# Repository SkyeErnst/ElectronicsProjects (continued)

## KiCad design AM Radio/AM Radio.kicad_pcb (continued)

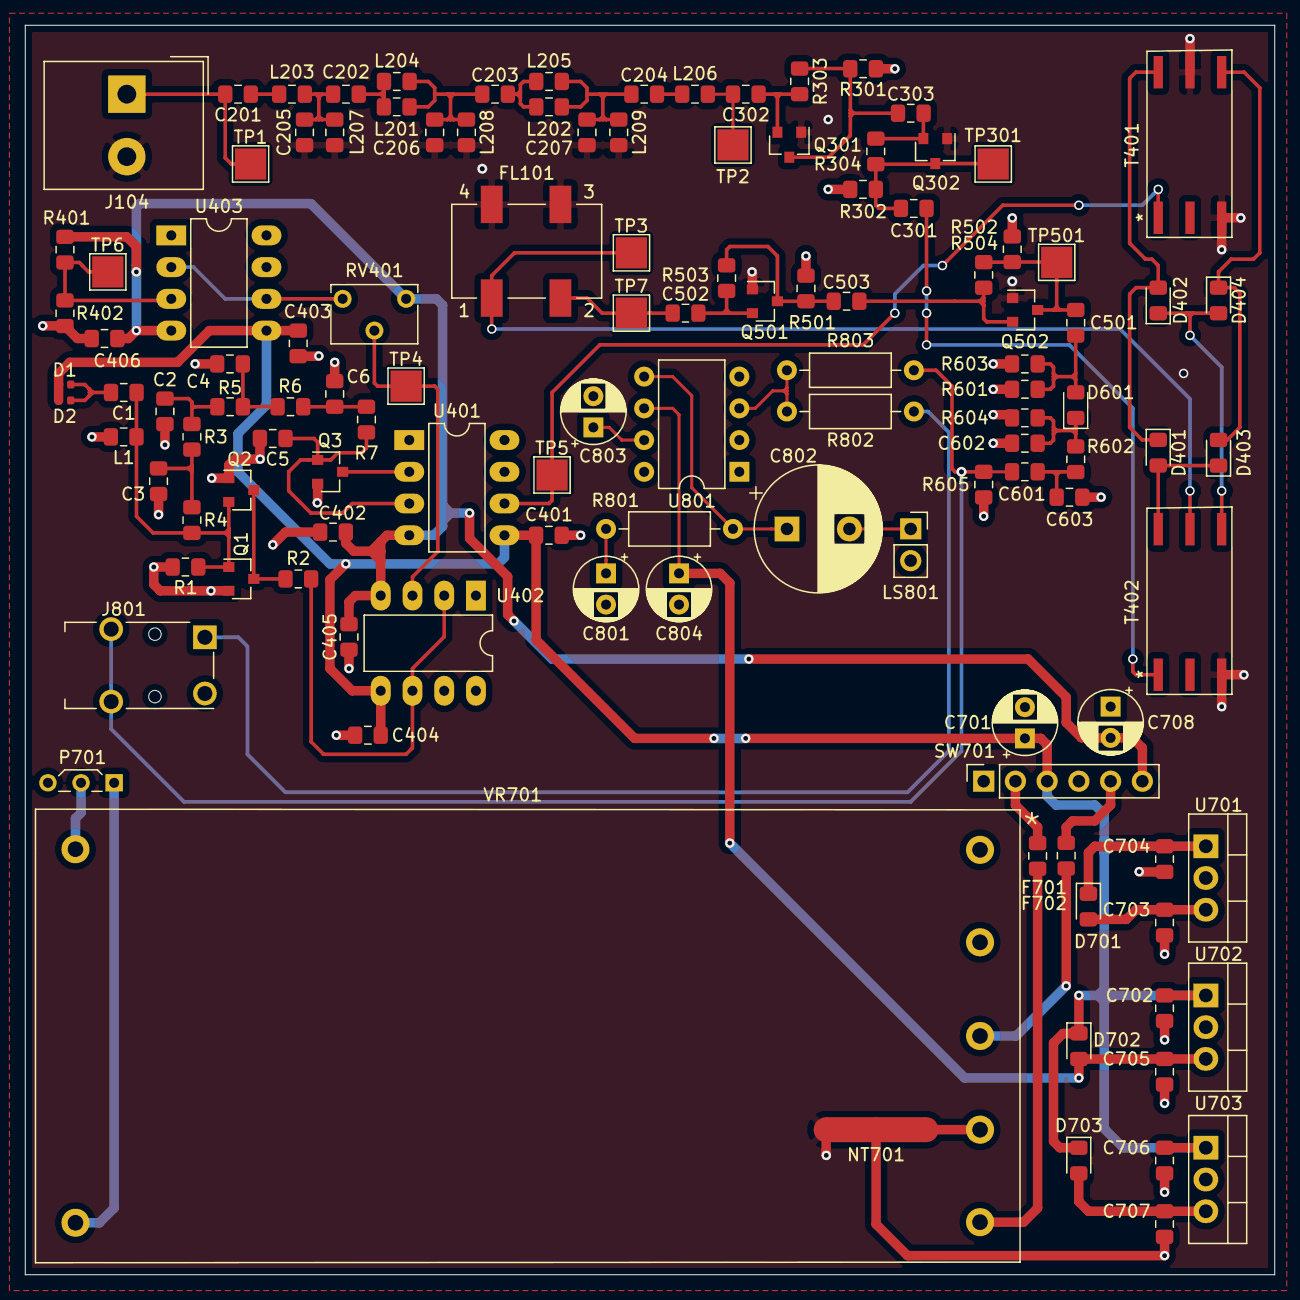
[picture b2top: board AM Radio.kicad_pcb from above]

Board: 4 copper layers, 100.0 x 100.0 mm, 121 parts (0 on the bottom side), 62 nets.

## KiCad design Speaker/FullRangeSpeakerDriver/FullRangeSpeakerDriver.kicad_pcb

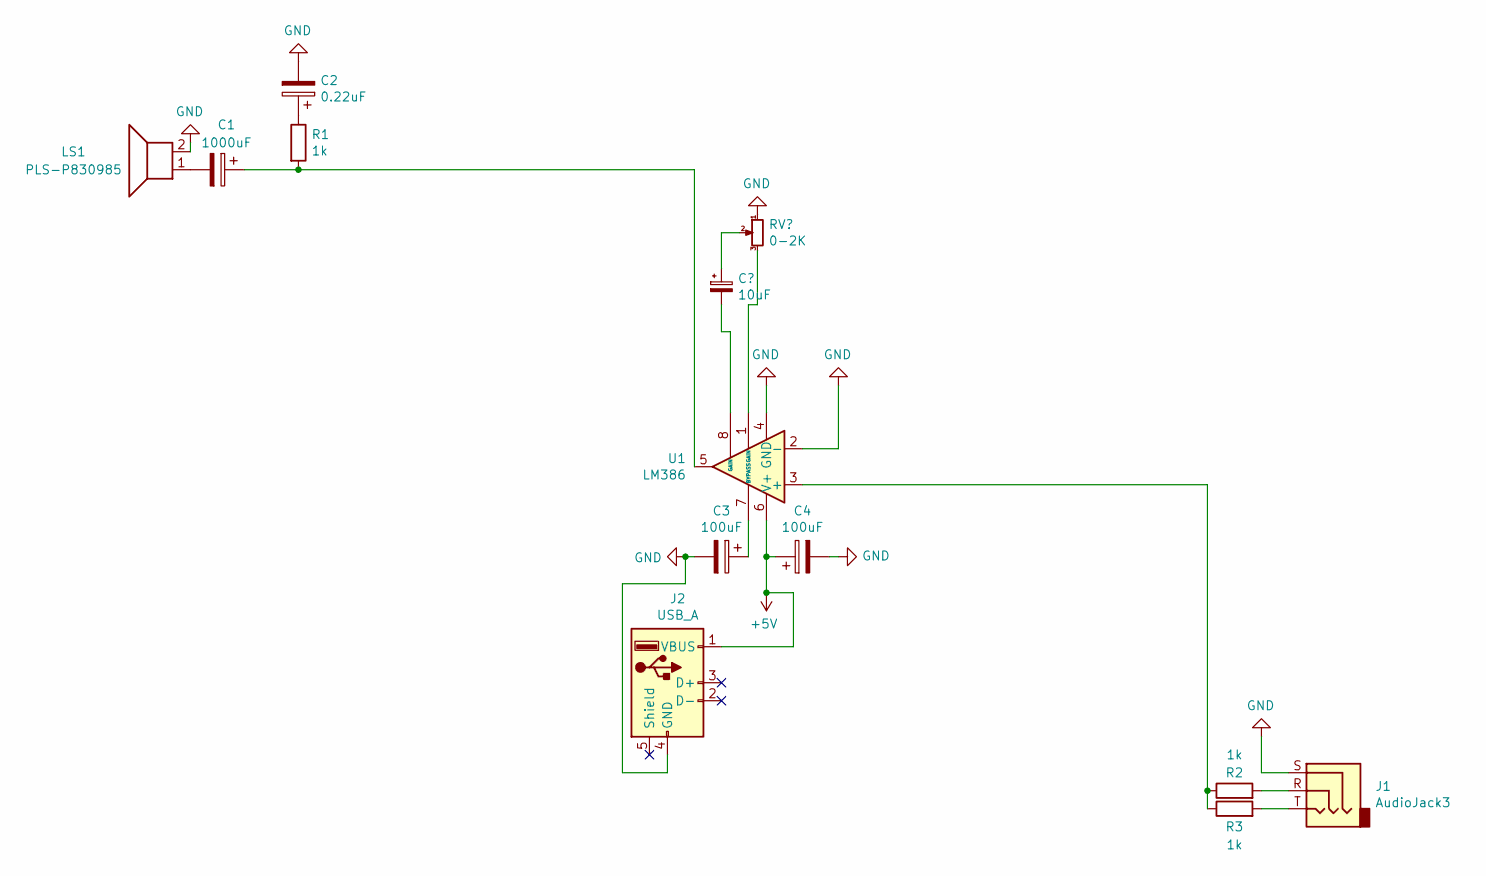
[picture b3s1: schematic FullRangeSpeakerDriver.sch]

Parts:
C1: 1000uF; CP_Radial_D10.0mm_P5.00mm
C2: 0.22uF; CP_Radial_D5.0mm_P2.50mm
C3, C4: 100uF; CP_Radial_D5.0mm_P2.50mm
J1: AudioJack3; PinSocket_1x03_P2.54mm_Vertical
J2: USB_A; USB_A_Stewart_SS-52100-001_Horizontal
LS1: PLS-P830985; PinSocket_1x02_P2.54mm_Vertical
R1, R2, R3: 1k; R_Axial_DIN0207_L6.3mm_D2.5mm_P10.16mm_Horizontal
U1: LM386; DIP-8_W7.62mm

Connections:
+15V: C4.1, J2.1 (VBUS), U1.6 (V+)
GND: C2.2, C3.2, C4.2, J1.S, J2.4 (GND), LS1.2, U1.2 (-), U1.4 (GND)
unnamed: C1.1, R1.2, U1.5
unnamed: C1.2, LS1.1
unnamed: C2.1, R1.1
unnamed: C3.1, U1.7 (BYPASS)
unnamed: J1.R, R2.2
unnamed: J1.T, R3.2
unnamed: R2.1, R3.1, U1.3 (+)

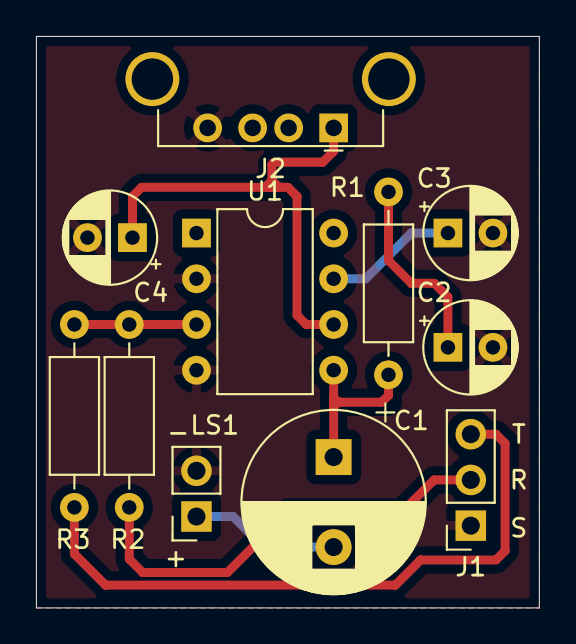
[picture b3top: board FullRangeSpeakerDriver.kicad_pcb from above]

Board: 2 copper layers, 27.9 x 31.7 mm, 11 parts (0 on the bottom side), 9 nets.

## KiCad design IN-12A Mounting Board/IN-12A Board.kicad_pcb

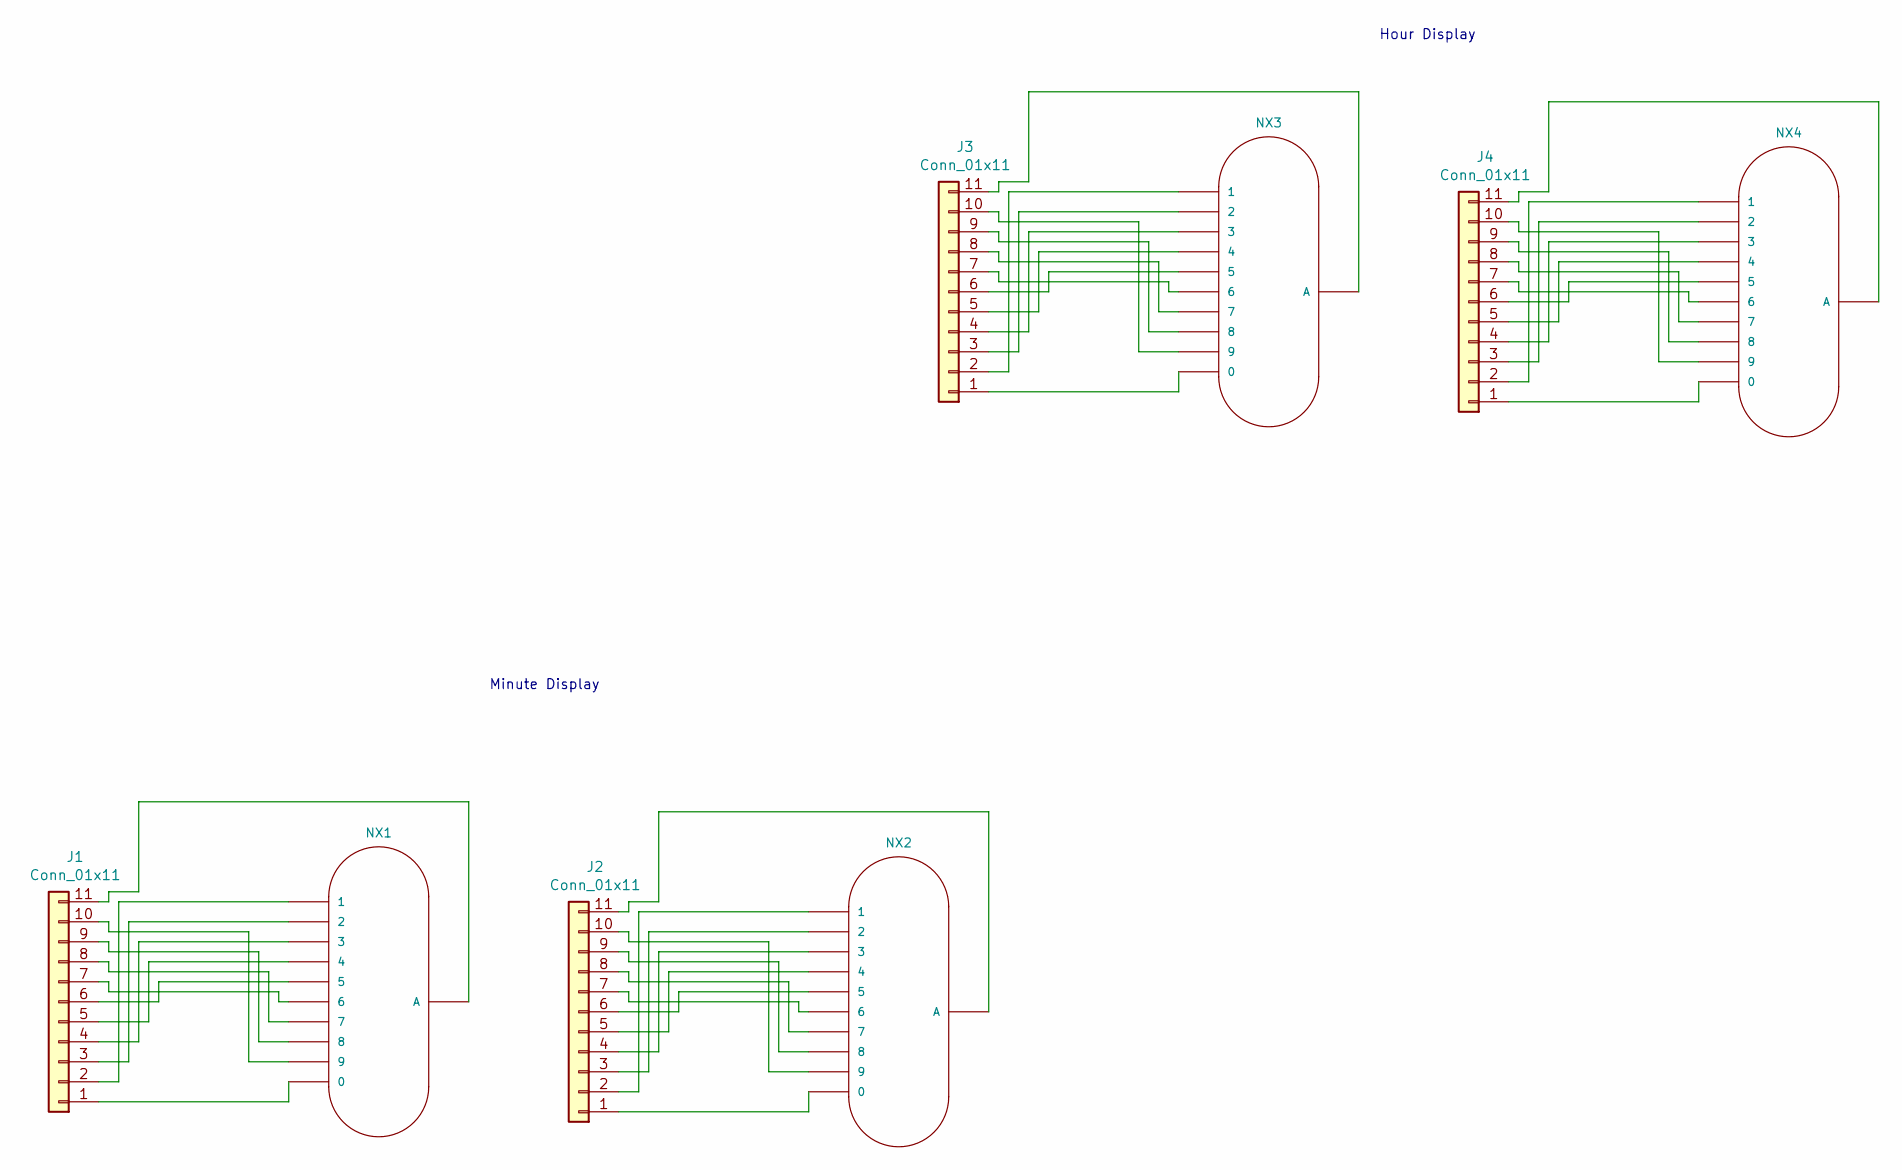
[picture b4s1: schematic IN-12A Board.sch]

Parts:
J1, J2, J3, J4: Conn_01x11; PinHeader_1x11_P2.54mm_Vertical
NX1, NX2, NX3, NX4: IN-12A; nixies-us-IN-12

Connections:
unnamed: J1.1, NX1.0
unnamed: J1.2, NX1.1
unnamed: J1.3, NX1.2
unnamed: J1.4, NX1.3
unnamed: J1.5, NX1.4
unnamed: J1.6, NX1.5
unnamed: J1.7, NX1.6
unnamed: J1.8, NX1.7
unnamed: J1.9, NX1.8
unnamed: J1.10, NX1.9
unnamed: J1.11, NX1.A
unnamed: J2.1, NX2.0
unnamed: J2.2, NX2.1
unnamed: J2.3, NX2.2
unnamed: J2.4, NX2.3
unnamed: J2.5, NX2.4
unnamed: J2.6, NX2.5
unnamed: J2.7, NX2.6
unnamed: J2.8, NX2.7
unnamed: J2.9, NX2.8
unnamed: J2.10, NX2.9
unnamed: J2.11, NX2.A
unnamed: J3.1, NX3.0
unnamed: J3.2, NX3.1
unnamed: J3.3, NX3.2
unnamed: J3.4, NX3.3
unnamed: J3.5, NX3.4
unnamed: J3.6, NX3.5
unnamed: J3.7, NX3.6
unnamed: J3.8, NX3.7
unnamed: J3.9, NX3.8
unnamed: J3.10, NX3.9
unnamed: J3.11, NX3.A
unnamed: J4.1, NX4.0
unnamed: J4.2, NX4.1
unnamed: J4.3, NX4.2
unnamed: J4.4, NX4.3
unnamed: J4.5, NX4.4
unnamed: J4.6, NX4.5
unnamed: J4.7, NX4.6
unnamed: J4.8, NX4.7
unnamed: J4.9, NX4.8
unnamed: J4.10, NX4.9
unnamed: J4.11, NX4.A

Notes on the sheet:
Hour Display
Minute Display

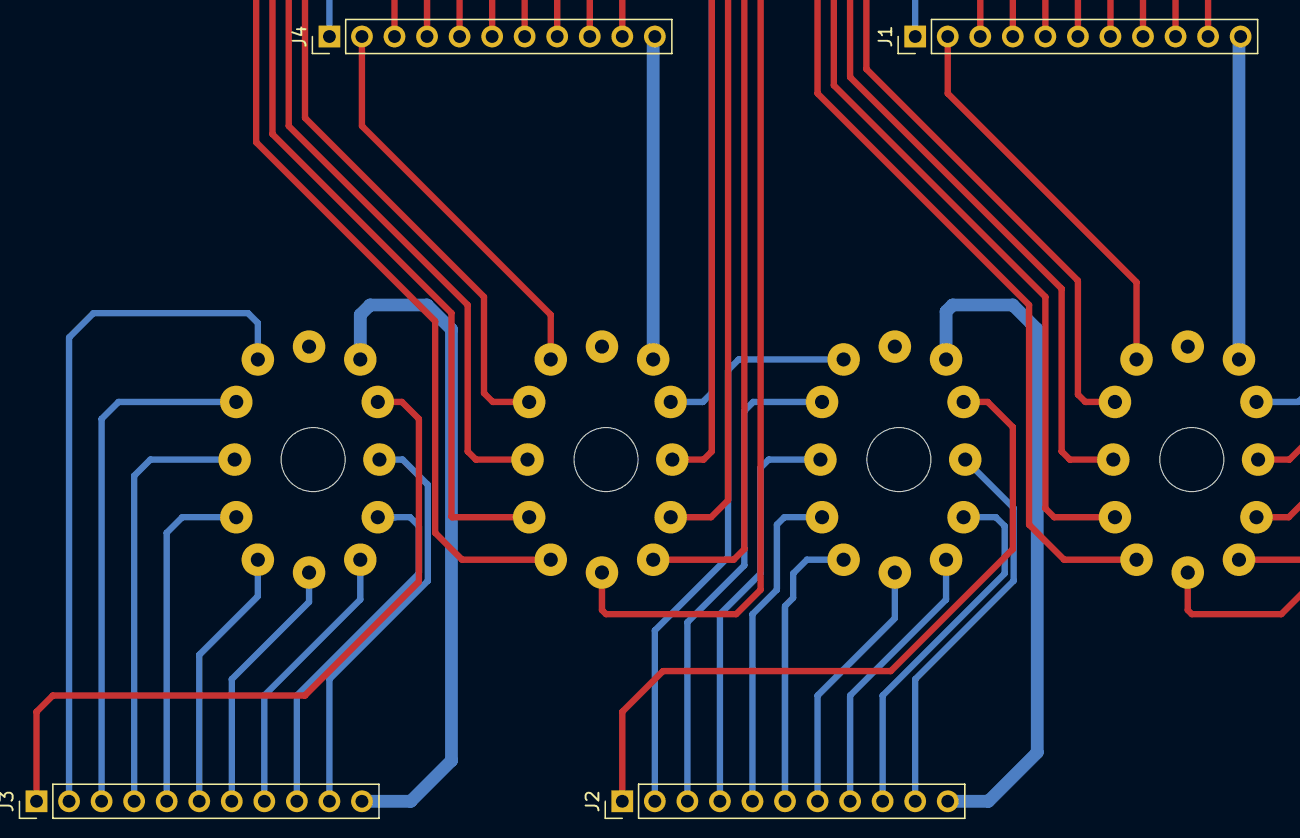
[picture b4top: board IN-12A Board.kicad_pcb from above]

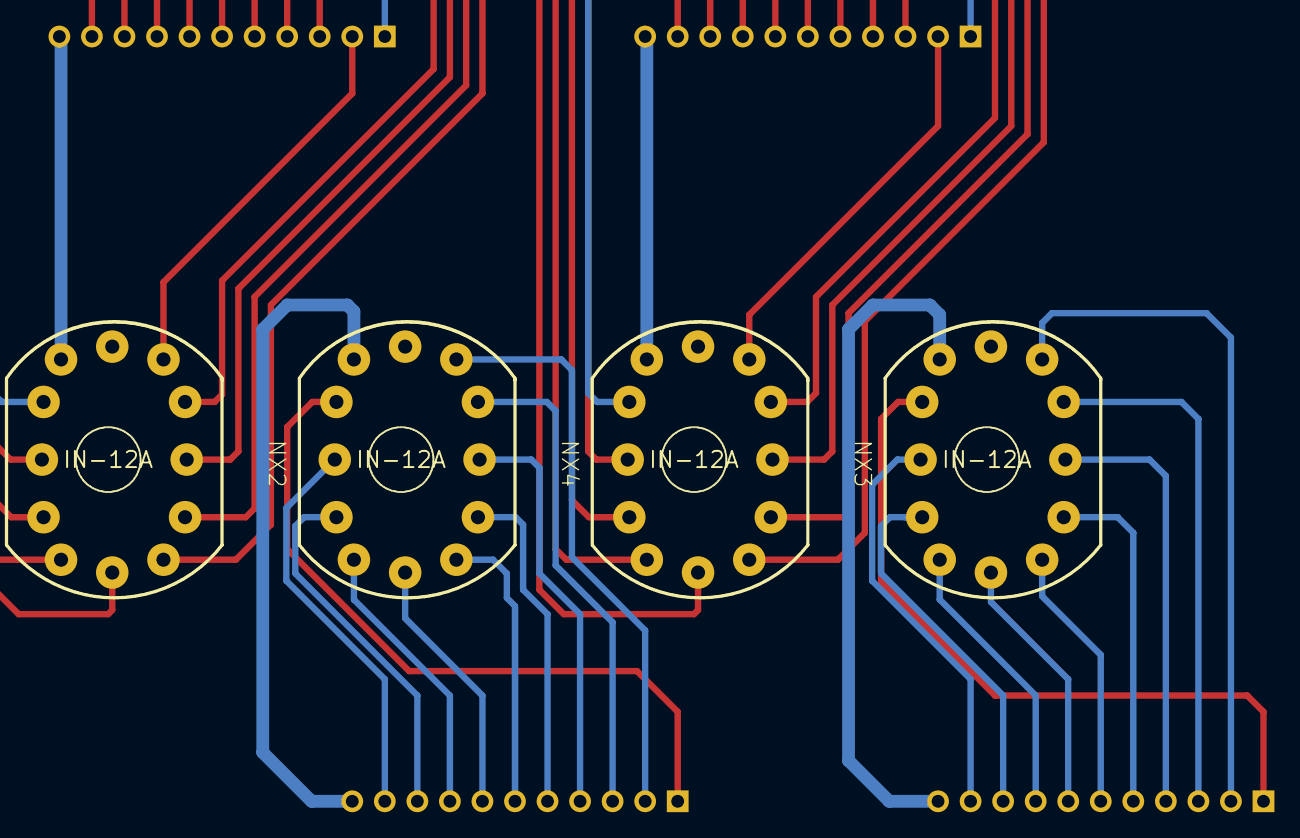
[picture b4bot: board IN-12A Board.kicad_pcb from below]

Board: 2 copper layers, 8 parts (4 on the bottom side), 44 nets.

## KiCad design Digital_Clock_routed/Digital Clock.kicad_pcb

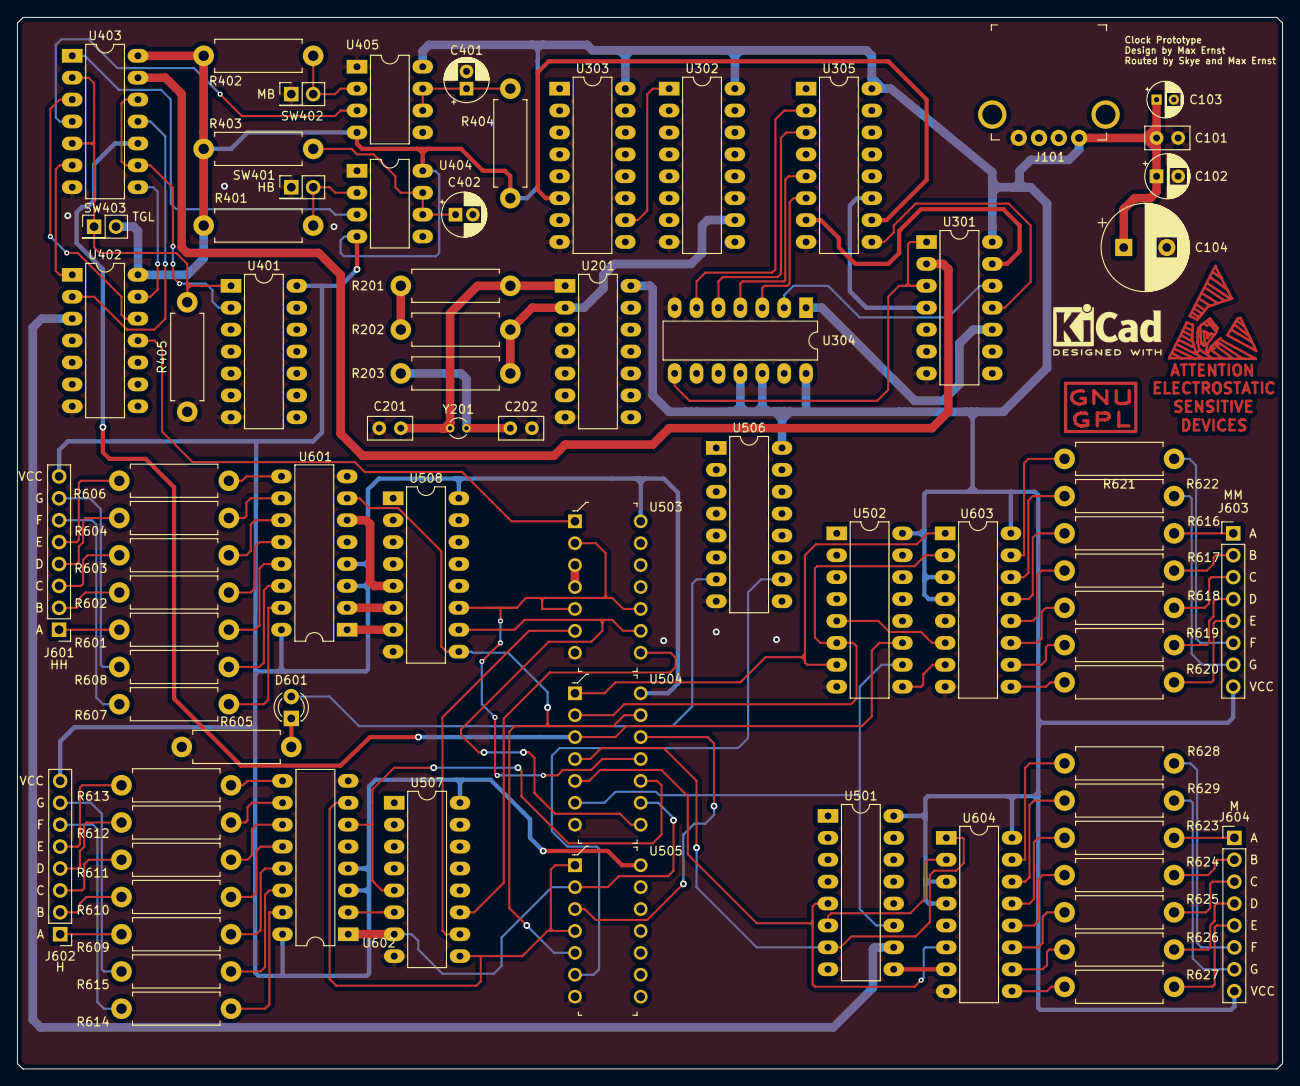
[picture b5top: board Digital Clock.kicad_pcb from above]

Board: 2 copper layers, 146.7 x 121.9 mm, 78 parts (0 on the bottom side), 116 nets.

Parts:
C101: 100nF; C_Disc_D5.0mm_W2.5mm_P2.50mm
C102: 1uF; CP_Radial_D5.0mm_P2.50mm
C103: 47uF; CP_Radial_D4.0mm_P2.00mm
C104: 1000uF; CP_Radial_D10.0mm_P5.00mm
C201, C202: 22pF; C_Disc_D5.0mm_W2.5mm_P2.50mm
C401, C402: 0.22uF; CP_Radial_D5.0mm_P2.00mm
D601: GREEN; LED_D3.0mm
J101: USB_A; USB_A_Female_UE27AC54100
J601, J602, J603, J604: Conn_01x08; PinHeader_1x08_P2.54mm_Vertical
R201, R202: 6.5Meg; R_Axial_DIN0411_L9.9mm_D3.6mm_P12.70mm_Horizontal
R203: 270k; R_Axial_DIN0411_L9.9mm_D3.6mm_P12.70mm_Horizontal
R401, R402, R405: 1k; R_Axial_DIN0411_L9.9mm_D3.6mm_P12.70mm_Horizontal
R403, R404: 1Meg; R_Axial_DIN0411_L9.9mm_D3.6mm_P12.70mm_Horizontal
R601, R602, R603, R604, R606, R607, R608, R609, R610, R611, R612, R613, R614, R615, R616, R617, R618, R619, R620, R621, R622, R623, R624, R625, R626, R627, R628, R629: 24; R_Axial_DIN0411_L9.9mm_D3.6mm_P12.70mm_Horizontal
R605: 220; R_Axial_DIN0411_L9.9mm_D3.6mm_P12.70mm_Horizontal
SW401: Hour_Button; PinHeader_2x01_P2.54mm_Vertical
SW402: Minute_Button; PinHeader_2x01_P2.54mm_Vertical
SW403: Toggle_Switch; PinHeader_2x01_P2.54mm_Vertical
U201: 74HCU04E; DIP-14_W7.62mm_LongPads
U301, U401: 74S04; DIP-14_W7.62mm_LongPads
U302, U303, U305: SN74HC4040N; DIP-16_W7.62mm_LongPads
U304: CD74HC30E; DIP-14_W7.62mm_LongPads
U402: SN74LS32N; DIP-14_W7.62mm_LongPads
U403: SN74HCT08N; DIP-14_W7.62mm_LongPads
U404, U405: NE555; DIP-8_W7.62mm_LongPads
U501, U502, U506, U507, U508: 4040; DIP-16_W7.62mm_LongPads
U503: SN74LS32N; DIP-14_W3mm
U504: SN74LS08N; DIP-14_W3mm
U505: SN74ALS08N; DIP-14_W3mm
U601, U602, U603, U604: 7447; DIP-16_W7.62mm_LongPads
Y201: 32.768kHz; Crystal_Round_D2.0mm_Vertical

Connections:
+5V: C101.1, C102.1, C103.1, C104.1, J101.1, J601.8, J602.8, J603.8, J604.8, R401.2, R402.2, R403.1, R404.1, SW403.2, U201.14, U301.14, U302.16, U303.16, U304.11, U304.12, U304.14, U305.16, U401.14, U402.14, U403.14, U404.4, U404.8, U405.4, U405.8, U501.16, U502.16, U503.14, U504.14, U505.14, U506.16, U507.16, U508.16, U601.3, U601.4, U601.16, U602.3, U602.4, U602.16, U603.3, U603.4, U603.16, U604.3, U604.4, U604.16
/ButtonLogic/1stPlaceHoursInput: U402.11, U503.1
/ButtonLogic/1stPlaceMinutesInput: U402.3, U501.10
/ButtonLogic/MinutesOutput: U403.10, U502.11, U504.3
/ButtonLogic/SecondsOutput: U301.2, U403.13
/DisplaySection/1stP_HH_O: U504.13, U505.5, U508.9, U601.7
/DisplaySection/1stP_H_O: U505.1, U505.4, U507.9, U602.7
/DisplaySection/1stP_MM_O: U502.9, U603.7
/DisplaySection/1stP_M_O: U501.9, U604.7
/DisplaySection/2ndP_HH_O: U508.7, U601.1
/DisplaySection/2ndP_H_O: U504.9, U505.2, U507.7, U602.1
/DisplaySection/2ndP_MM_O: U502.7, U504.1, U603.1
/DisplaySection/2ndP_M_O: U501.7, U504.4, U604.1
/DisplaySection/3rdP_HH_O: U508.6, U601.2
/DisplaySection/3rdP_H_O: U507.6, U602.2
/DisplaySection/3rdP_MM_O: U502.6, U504.2, U603.2
/DisplaySection/3rdP_M_O: U501.6, U604.2
/DisplaySection/4thP_HH_O: U508.5, U601.6
/DisplaySection/4thP_H_O: U504.10, U507.5, U602.6
/DisplaySection/4thP_MM_O: U502.5, U603.6
/DisplaySection/4thP_M_O: U501.5, U504.5, U604.6
/DisplaySection/AM_PM_INDICATOR: D601.2, U506.7
/Oscillator/Oscillator32768Output: R202.1, R203.1, U201.2, U302.10
GND: C101.2, C102.2, C103.2, C104.2, C201.2, C202.2, C401.2, C402.2, J101.4, R405.1, R605.1, SW401.1, SW402.1, U201.7, U301.7, U302.8, U302.11, U303.8, U303.11, U304.7, U305.8, U401.7, U402.7, U403.7, U404.1, U405.1, U501.8, U502.8, U503.7, U504.7, U505.7, U506.8, U507.8, U508.8, U601.8, U602.8, U603.8, U604.8
unnamed: C201.1, R201.2, U201.1, Y201.1
unnamed: C202.1, R203.2, Y201.2
unnamed: C401.1, R404.2, U405.6, U405.7
unnamed: C402.1, R403.2, U404.6, U404.7
unnamed: D601.1, R605.2
unnamed: J601.1, R601.1
unnamed: J601.2, R602.1
unnamed: J601.3, R603.1
unnamed: J601.4, R604.1
unnamed: J601.5, R606.1
unnamed: J601.6, R607.1
unnamed: J601.7, R608.1
unnamed: J602.1, R609.1
unnamed: J602.2, R610.1
unnamed: J602.3, R611.1
unnamed: J602.4, R612.1
unnamed: J602.5, R613.1
unnamed: J602.6, R614.1
unnamed: J602.7, R615.1
unnamed: J603.1, R616.1
unnamed: J603.2, R617.1
unnamed: J603.3, R618.1
unnamed: J603.4, R619.1
unnamed: J603.5, R620.1
unnamed: J603.6, R621.1
unnamed: J603.7, R622.1
unnamed: J604.1, R623.1
unnamed: J604.2, R624.1
unnamed: J604.3, R625.1
unnamed: J604.4, R626.1
unnamed: J604.5, R627.1
unnamed: J604.6, R628.1
unnamed: J604.7, R629.1
unnamed: R201.1, R202.2
unnamed: R401.1, SW401.2, U404.2
unnamed: R402.1, SW402.2, U405.2
unnamed: R405.2, SW403.1, U401.1, U403.2, U403.5
unnamed: R601.2, U601.13
unnamed: R602.2, U601.12
unnamed: R603.2, U601.11
unnamed: R604.2, U601.10
unnamed: R606.2, U601.9
unnamed: R607.2, U601.15
unnamed: R608.2, U601.14
unnamed: R609.2, U602.13
unnamed: R610.2, U602.12
unnamed: R611.2, U602.11
unnamed: R612.2, U602.10
unnamed: R613.2, U602.9
unnamed: R614.2, U602.15
unnamed: R615.2, U602.14
unnamed: R616.2, U603.13
unnamed: R617.2, U603.12
unnamed: R618.2, U603.11
unnamed: R619.2, U603.10
unnamed: R620.2, U603.9
unnamed: R621.2, U603.15
unnamed: R622.2, U603.14
unnamed: R623.2, U604.13
unnamed: R624.2, U604.12
unnamed: R625.2, U604.11
unnamed: R626.2, U604.10
unnamed: R627.2, U604.9
unnamed: R628.2, U604.15
unnamed: R629.2, U604.14
unnamed: U301.1, U301.3, U304.8
unnamed: U301.4, U305.11
unnamed: U301.10, U304.1
unnamed: U301.11, U305.9
unnamed: U301.12, U304.2
unnamed: U301.13, U305.7
unnamed: U302.1, U303.10
unnamed: U303.6, U305.10
unnamed: U304.3, U305.6
unnamed: U304.4, U305.5
unnamed: U304.5, U305.3
unnamed: U304.6, U305.2
unnamed: U401.2, U403.9, U403.12
unnamed: U402.1, U403.6
unnamed: U402.2, U403.11
unnamed: U402.12, U403.3
unnamed: U402.13, U403.8
unnamed: U403.1, U404.3
unnamed: U403.4, U405.3
unnamed: U501.11, U502.10, U504.6
unnamed: U503.3, U503.4
unnamed: U503.6, U507.10
unnamed: U503.8, U507.11
unnamed: U503.9, U504.8, U508.10
unnamed: U503.2, U503.5, U503.10, U504.11, U508.11
unnamed: U504.12, U505.3
unnamed: U505.6, U506.10

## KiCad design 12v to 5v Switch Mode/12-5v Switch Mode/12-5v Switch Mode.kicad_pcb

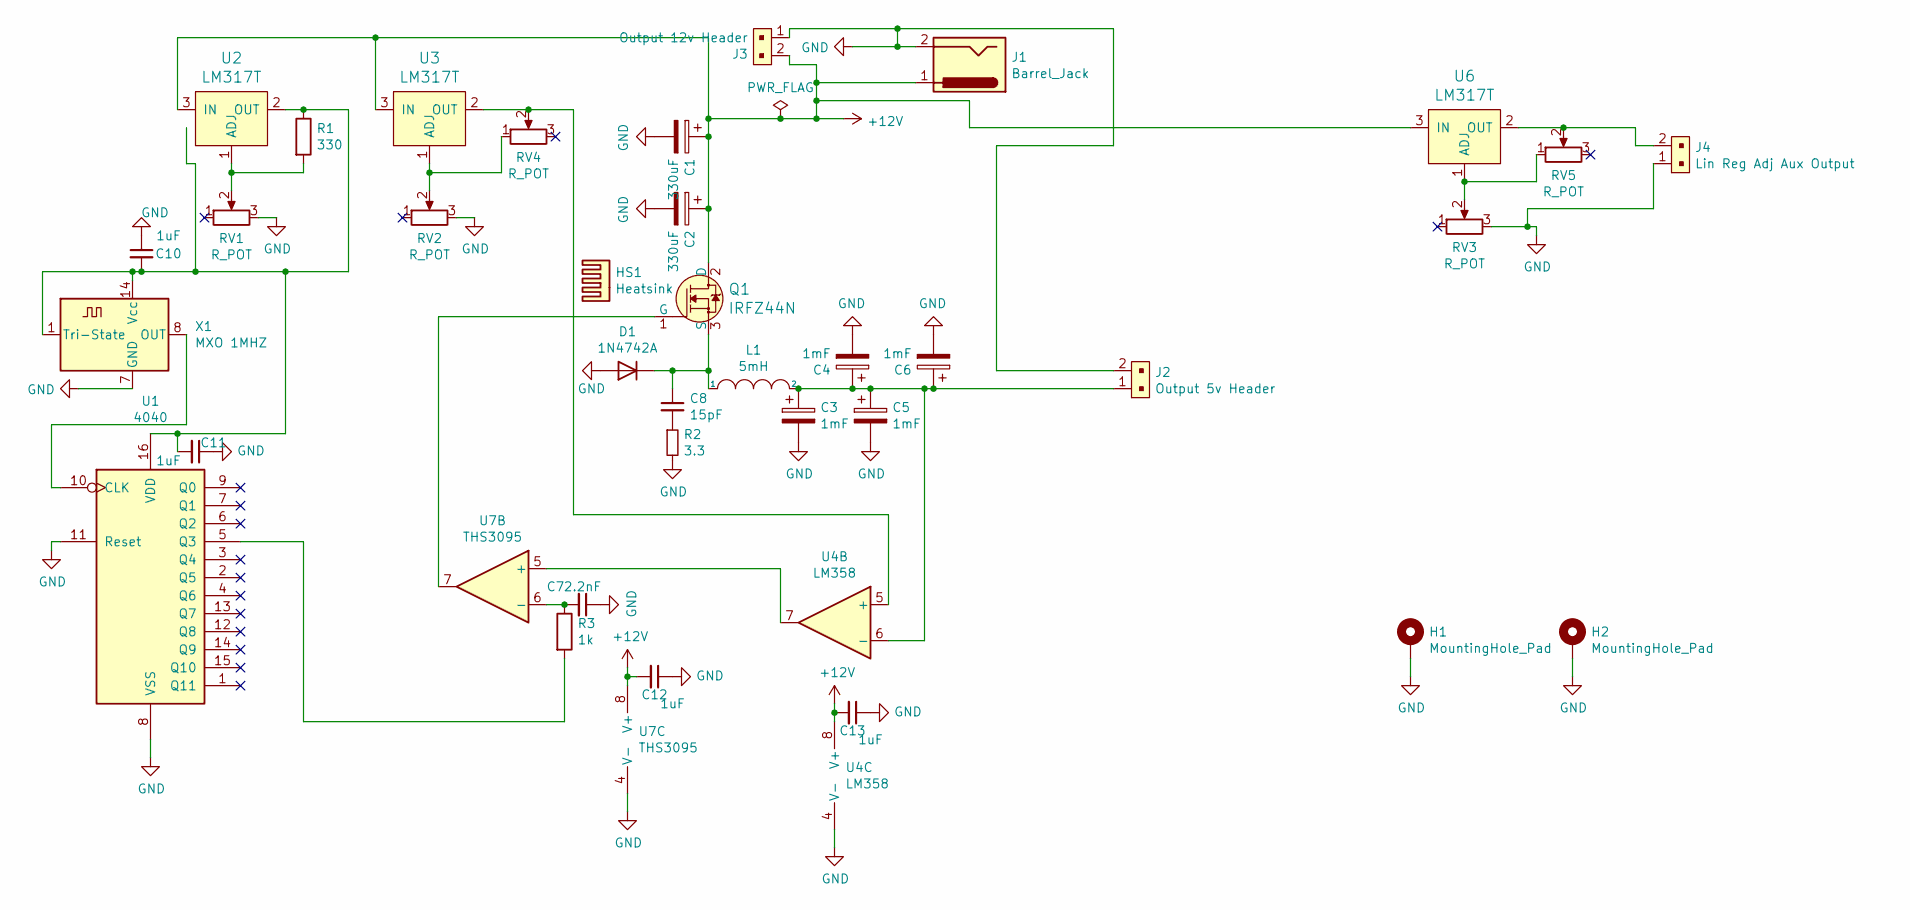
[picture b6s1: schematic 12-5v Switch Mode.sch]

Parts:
C1, C2: 330uF; CP_Radial_D12.5mm_P5.00mm
C3, C4, C5, C6: 1mF; CP_Radial_D12.5mm_P5.00mm
C7: 2.2nF; CP_Radial_D4.0mm_P1.50mm
C8: 15pF; CP_Radial_D4.0mm_P1.50mm
C10, C11, C12, C13: 1uF; C_0805_2012Metric
D1: 1N4742A; D_DO-41_SOD81_P7.62mm_Horizontal
H1, H2: MountingHole_Pad; MountingHole_2.2mm_M2_Pad
HS1: Heatsink; Heatsink VM1-038-1AE
J1: Barrel_Jack; CUI_PJ-063AH
J2: Output 5v Header; PinHeader_1x2_P2.54mm; MPN 22-23-2021; Digi-Key_PN WM4200-ND
J3: Output 12v Header; PinHeader_1x2_P2.54mm; MPN 22-23-2021; Digi-Key_PN WM4200-ND
J4: Lin Reg Adj Aux Output; PinHeader_1x2_P2.54mm; MPN 22-23-2021; Digi-Key_PN WM4200-ND
L1: 5mH; L_Radial_D50.8mm_P33.27mm_Vishay_IHB-6
Q1: IRFZ44N; TO-220-3; MPN IRFZ44N; Digi-Key_PN IRFZ44N
R1: 330; R_Axial_DIN0207_L6.3mm_D2.5mm_P10.16mm_Horizontal
R2: 3.3; R_Axial_DIN0207_L6.3mm_D2.5mm_P10.16mm_Horizontal
R3: 1k; R_Axial_DIN0207_L6.3mm_D2.5mm_P10.16mm_Horizontal
RV1, RV2, RV3, RV4, RV5: R_POT; Potentiometer_Bourns_3299W_Vertical
U1: 4040; DIP-16_W7.62mm
U2, U3, U6: LM317T; TO-220-3; MPN LM317T; Digi-Key_PN 497-1575-5-ND
U4: LM358; DIP-8_W7.62mm
U7: THS3095; SOIC-8_3.9x4.9mm_P1.27mm
X1: MXO 1MHZ; Oscillator_DIP-14

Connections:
+12V: C1.1, C2.1, C12.2, C13.2, J1.1, J3.2, Q1.2 (D), U2.3 (IN), U3.3 (IN), U4.8 (V+), U6.3 (IN), U7.8 (V+)
GND: C1.2, C2.2, C3.2, C4.2, C5.2, C6.2, C7.1, C10.1, C11.1, C12.1, C13.1, D1.1 (A), H1.1, H2.1, J1.2, J2.2, J3.1, J4.1, R2.2, RV1.3, RV2.3, RV3.3, U1.8 (VSS), U1.11 (Reset), U4.4 (V-), U7.4 (V-), X1.7 (GND)
unnamed: C3.1, C4.1, C5.1, C6.1, J2.1, L1.2, U4.6 (-)
unnamed: C7.2, R3.1, U7.6 (-)
unnamed: C8.1, D1.2 (K), L1.1, Q1.3 (S)
unnamed: C8.2, R2.1
unnamed: C10.2, C11.2, R1.1, U1.16 (VDD), U2.2 (OUT), X1.1 (Tri-State), X1.14 (Vcc)
unnamed: J4.2, RV5.2, U6.2 (OUT)
unnamed: Q1.1 (G), U7.7
unnamed: R1.2, RV1.2, U2.1 (ADJ)
unnamed: R3.2, U1.5 (Q3)
unnamed: RV2.2, RV4.1, U3.1 (ADJ)
unnamed: RV3.2, RV5.1, U6.1 (ADJ)
unnamed: RV4.2, U3.2 (OUT), U4.5 (+)
unnamed: U1.10 (CLK), X1.8 (OUT)
unnamed: U4.7, U7.5 (+)

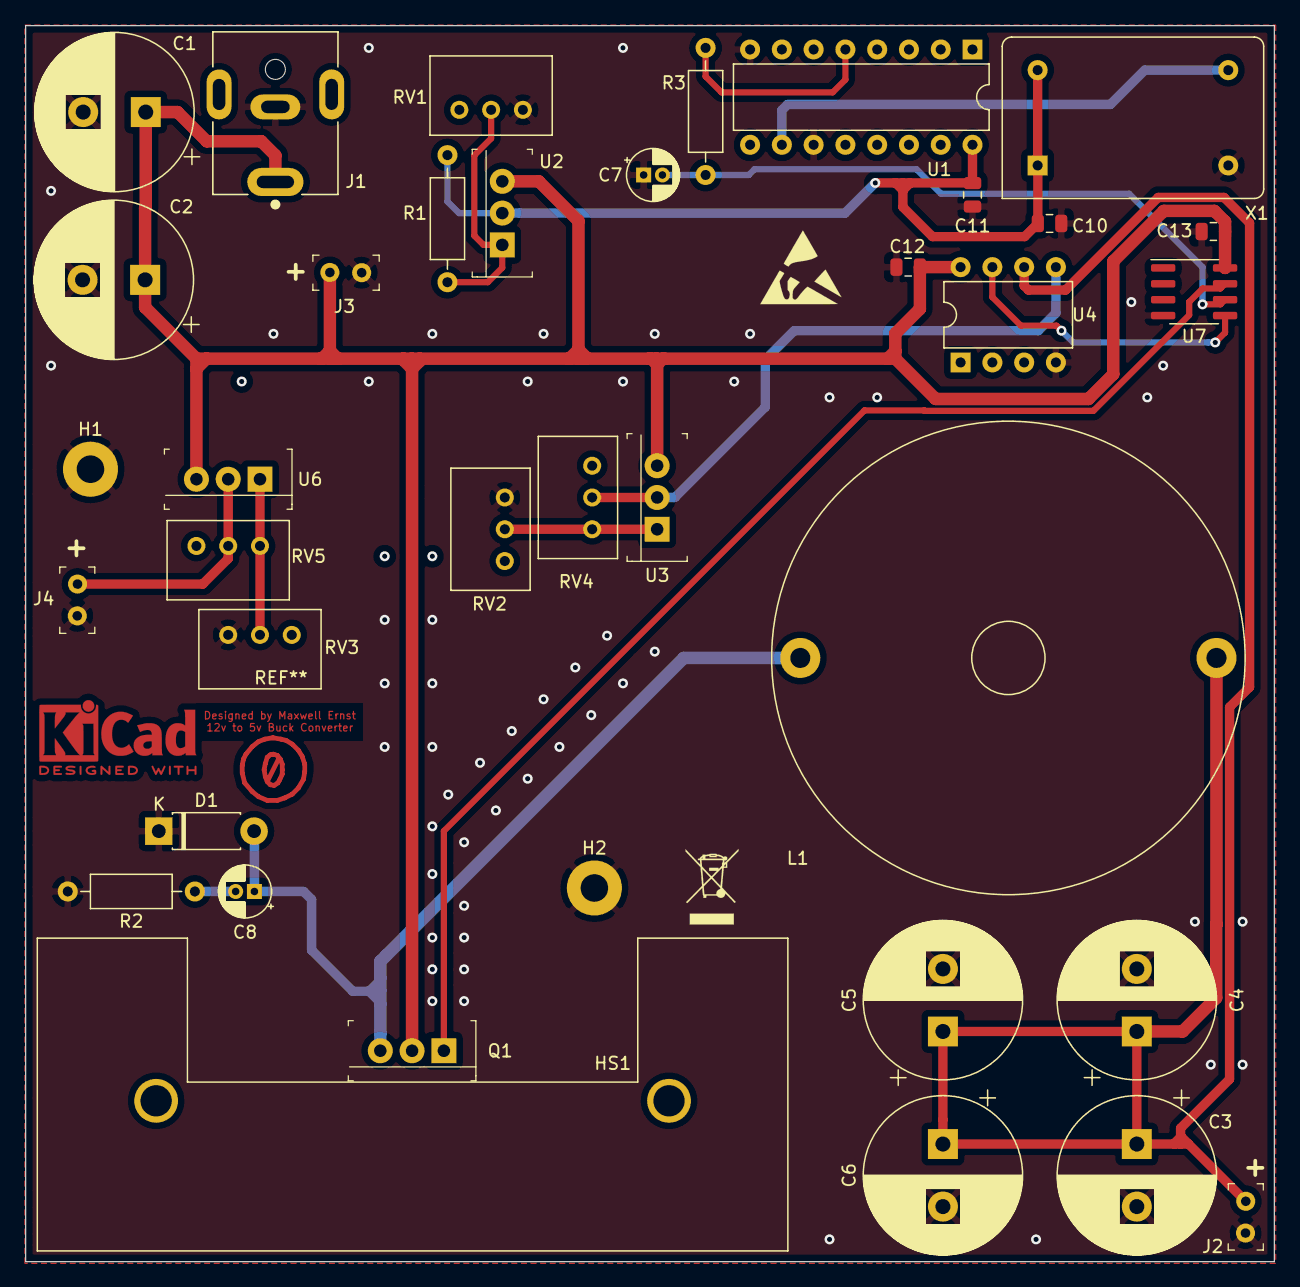
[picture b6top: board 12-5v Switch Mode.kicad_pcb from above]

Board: 2 copper layers, 99.8 x 98.8 mm, 37 parts (0 on the bottom side), 16 nets.

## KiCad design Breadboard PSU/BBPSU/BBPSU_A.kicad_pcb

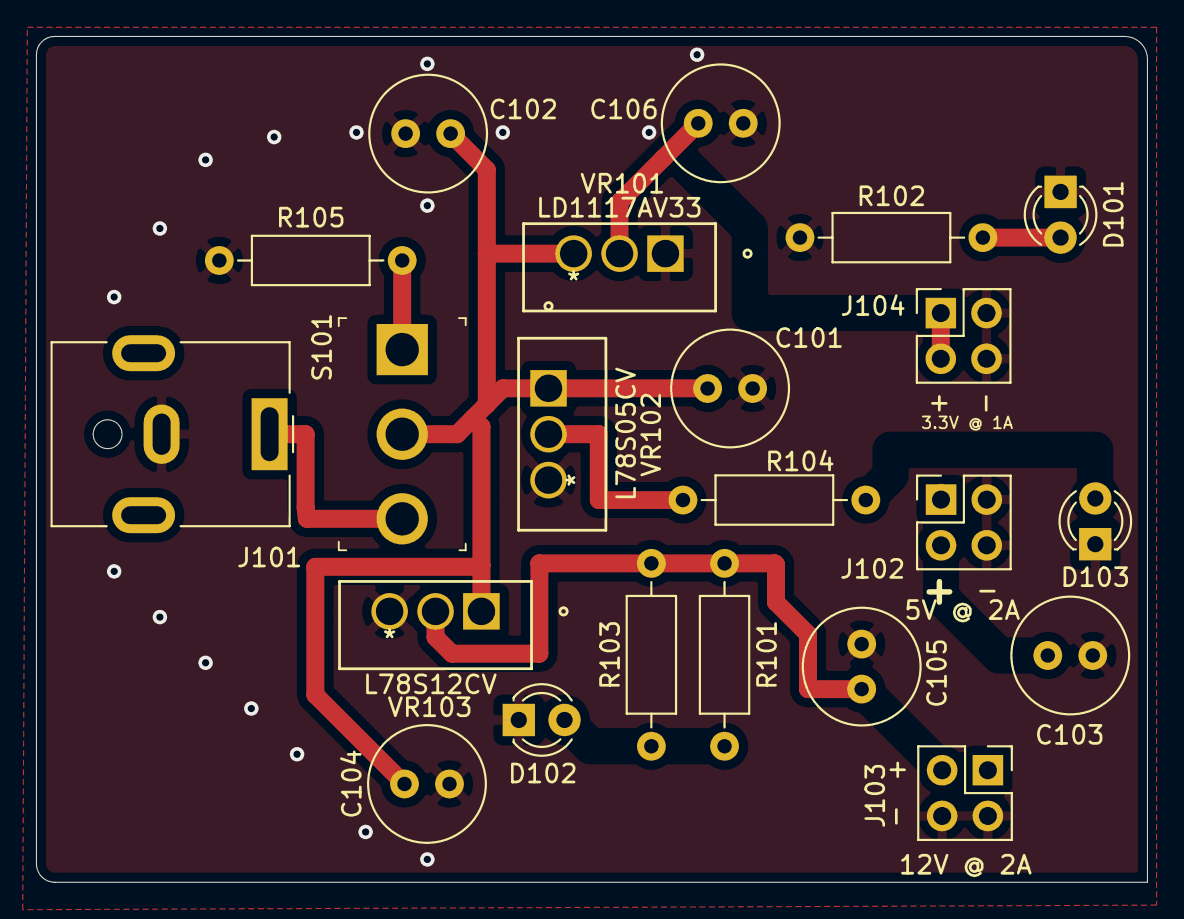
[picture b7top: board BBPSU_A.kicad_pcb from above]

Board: 2 copper layers, 61.7 x 47.0 mm, 22 parts (0 on the bottom side), 10 nets.

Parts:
C101, C104: 0.33uF; C_Radial_D6.3mm_H11.0mm_P2.50mm
C102, C103, C105: 0.1uF; C_Radial_D6.3mm_H11.0mm_P2.50mm
C106: 10uF; C_Radial_D6.3mm_H11.0mm_P2.50mm
D101, D102, D103: 151031VS04000; LED_D3.0mm
J101: PJ-063AH; BarrelJack_CUI_PJ-063AH_Horizontal
J102, J103, J104: 2.54mm pitch; PinHeader_2x02_P2.54mm_Vertical
R101, R102, R103, R104: 500; R_Axial_DIN0207_L6.3mm_D2.5mm_P10.16mm_Horizontal
R105: 100K; R_Axial_DIN0207_L6.3mm_D2.5mm_P10.16mm_Horizontal
S101: 100SP1T1B4M2QE; Toggle_Switch_100SP1T1B4M2QE
VR101: LD1117AV33
VR102: L78S05CV
VR103: L78S12CV

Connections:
+3V3: C106.1, J104.1, J104.3, VR101.2
+5V: C103.1, J102.1, J102.3, R104.1, VR102.2
+12V: C105.1, J103.1, J103.3, R101.1, R103.1, VR103.2
GND: C101.2, C102.1, C103.2, C104.2, C105.2, C106.2, D101.1, D102.1, D103.1, J101.2, J102.2, J102.4, J103.2, J103.4, J104.2, J104.4, R102.1, R105.1, VR101.1, VR102.3, VR103.3
unnamed: C101.1, C102.2, C104.1, S101.2, VR101.3, VR102.1, VR103.1
unnamed: D101.2, R102.2
unnamed: D102.2, R101.2, R103.2
unnamed: D103.2, R104.2
unnamed: R105.2, S101.1
PWR_IN: J101.1, S101.3

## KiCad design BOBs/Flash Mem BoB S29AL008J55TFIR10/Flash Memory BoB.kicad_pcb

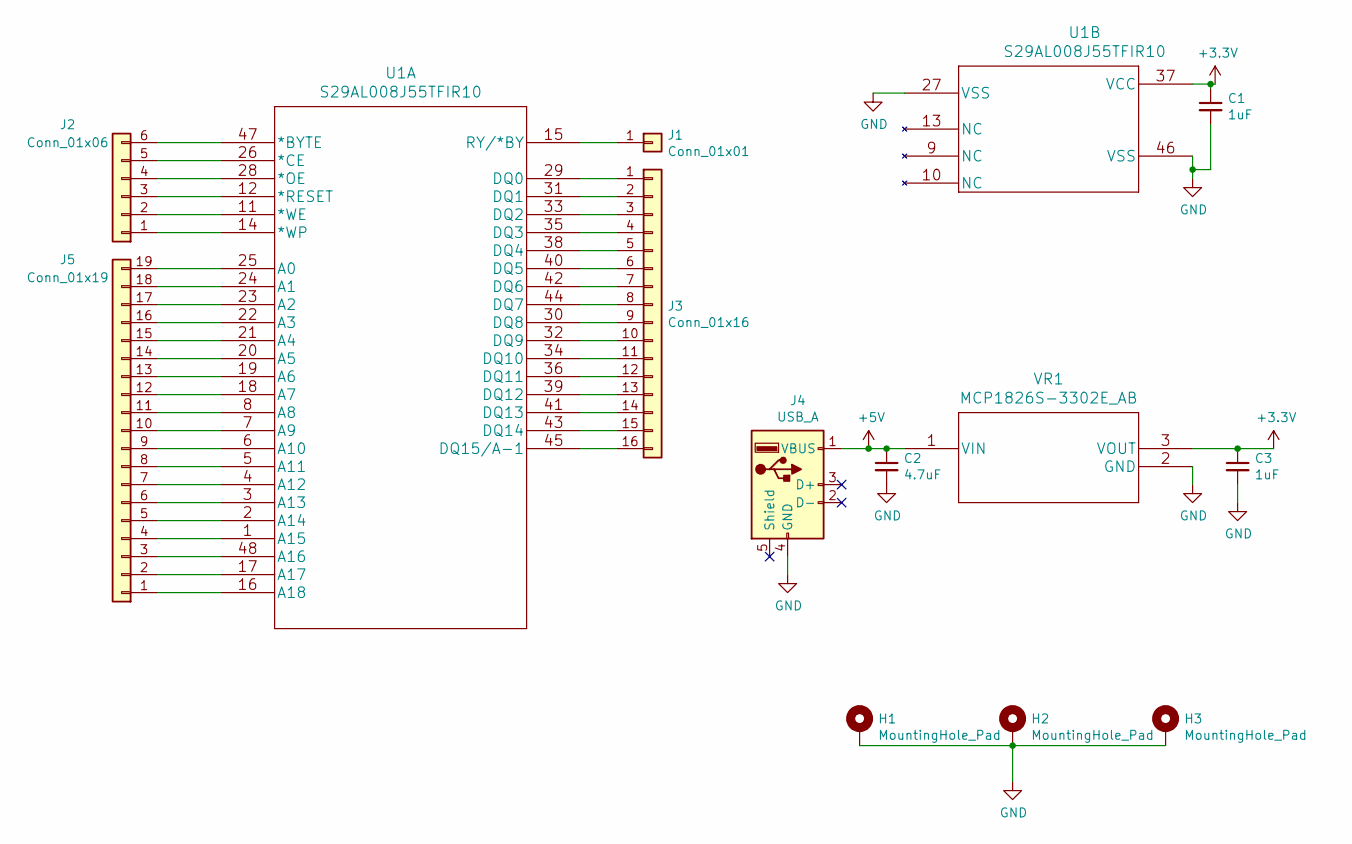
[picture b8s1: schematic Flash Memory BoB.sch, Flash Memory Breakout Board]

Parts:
C1, C3: 1uF; C_Disc_D3.8mm_W2.6mm_P2.50mm
C2: 4.7uF; C_Disc_D4.3mm_W1.9mm_P5.00mm
H1, H2, H3: MountingHole_Pad; MountingHole_2.2mm_M2_Pad_Via
J1: Conn_01x01; PinSocket_1x01_P2.54mm_Vertical
J2: Conn_01x06; PinSocket_1x06_P2.54mm_Vertical
J3: Conn_01x16; PinSocket_1x16_P2.54mm_Vertical
J4: USB_A; USB_A_Female_UE27AC54100
J5: Conn_01x19; PinSocket_1x19_P2.54mm_Vertical
U1: S29AL008J55TFIR10
VR1: MCP1826S-3302E_AB; TO-220-3_Vertical

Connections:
+3V3: C1.1, C3.1, U1.37 (VCC), VR1.3 (VOUT)
+5V: C2.1, J4.1 (VBUS), VR1.1 (VIN)
GND: C1.2, C2.2, C3.2, H1.1, H2.1, H3.1, J4.4 (GND), U1.27 (VSS), U1.46 (VSS), VR1.2 (GND)
unnamed: J1.1, U1.15 (RY/*BY)
unnamed: J2.1, U1.14 (*WP)
unnamed: J2.2, U1.11 (*WE)
unnamed: J2.3, U1.12 (*RESET)
unnamed: J2.4, U1.28 (*OE)
unnamed: J2.5, U1.26 (*CE)
unnamed: J2.6, U1.47 (*BYTE)
unnamed: J3.1, U1.29 (DQ0)
unnamed: J3.2, U1.31 (DQ1)
unnamed: J3.3, U1.33 (DQ2)
unnamed: J3.4, U1.35 (DQ3)
unnamed: J3.5, U1.38 (DQ4)
unnamed: J3.6, U1.40 (DQ5)
unnamed: J3.7, U1.42 (DQ6)
unnamed: J3.8, U1.44 (DQ7)
unnamed: J3.9, U1.30 (DQ8)
unnamed: J3.10, U1.32 (DQ9)
unnamed: J3.11, U1.34 (DQ10)
unnamed: J3.12, U1.36 (DQ11)
unnamed: J3.13, U1.39 (DQ12)
unnamed: J3.14, U1.41 (DQ13)
unnamed: J3.15, U1.43 (DQ14)
unnamed: J3.16, U1.45 (DQ15/A-1)
unnamed: J5.1, U1.16 (A18)
unnamed: J5.2, U1.17 (A17)
unnamed: J5.3, U1.48 (A16)
unnamed: J5.4, U1.1 (A15)
unnamed: J5.5, U1.2 (A14)
unnamed: J5.6, U1.3 (A13)
unnamed: J5.7, U1.4 (A12)
unnamed: J5.8, U1.5 (A11)
unnamed: J5.9, U1.6 (A10)
unnamed: J5.10, U1.7 (A9)
unnamed: J5.11, U1.8 (A8)
unnamed: J5.12, U1.18 (A7)
unnamed: J5.13, U1.19 (A6)
unnamed: J5.14, U1.20 (A5)
unnamed: J5.15, U1.21 (A4)
unnamed: J5.16, U1.22 (A3)
unnamed: J5.17, U1.23 (A2)
unnamed: J5.18, U1.24 (A1)
unnamed: J5.19, U1.25 (A0)
